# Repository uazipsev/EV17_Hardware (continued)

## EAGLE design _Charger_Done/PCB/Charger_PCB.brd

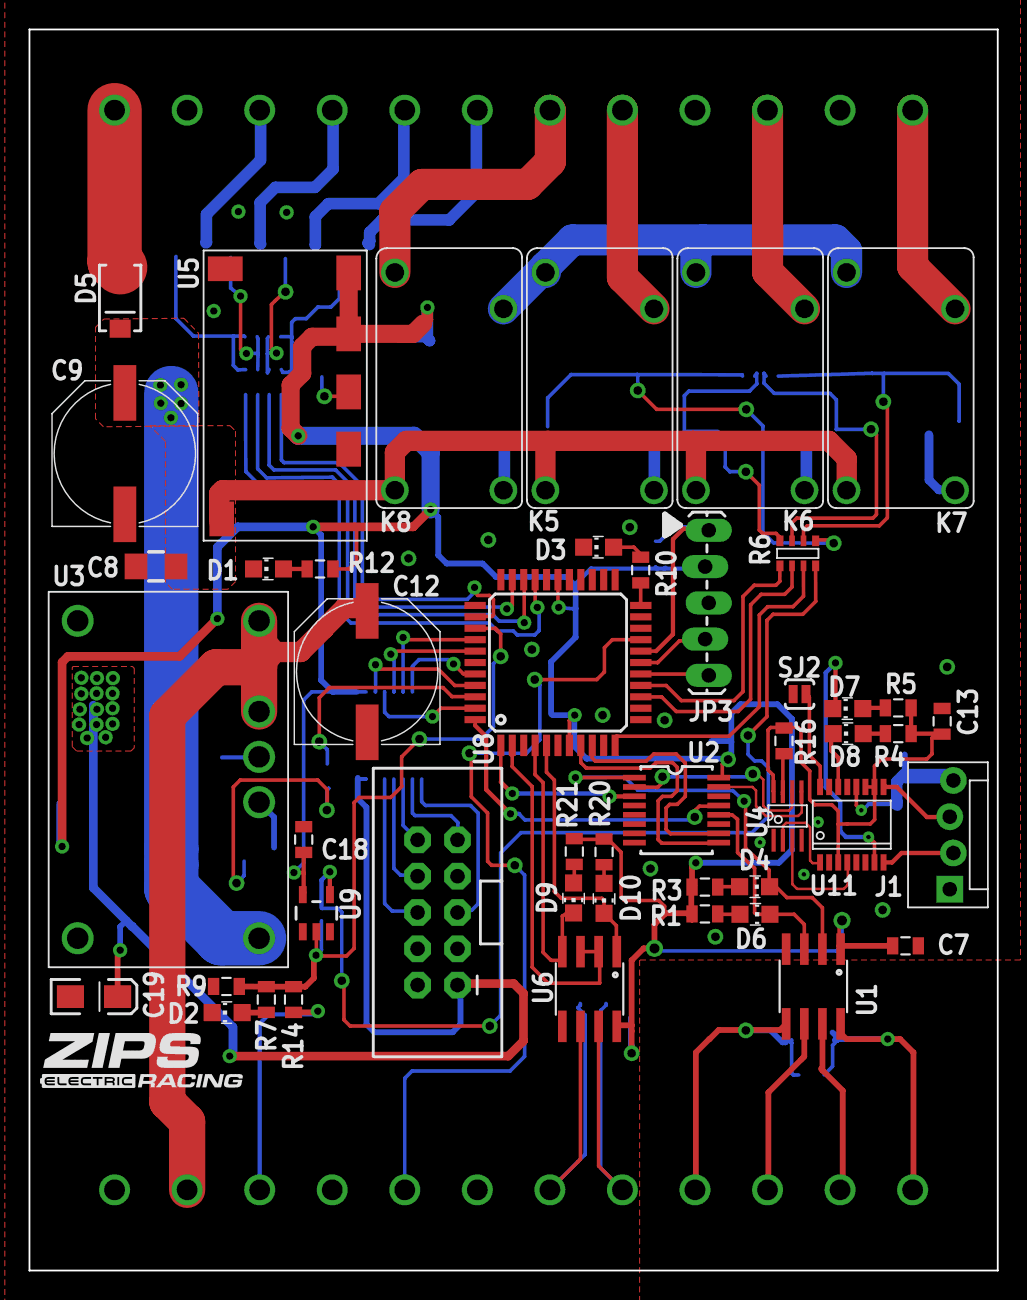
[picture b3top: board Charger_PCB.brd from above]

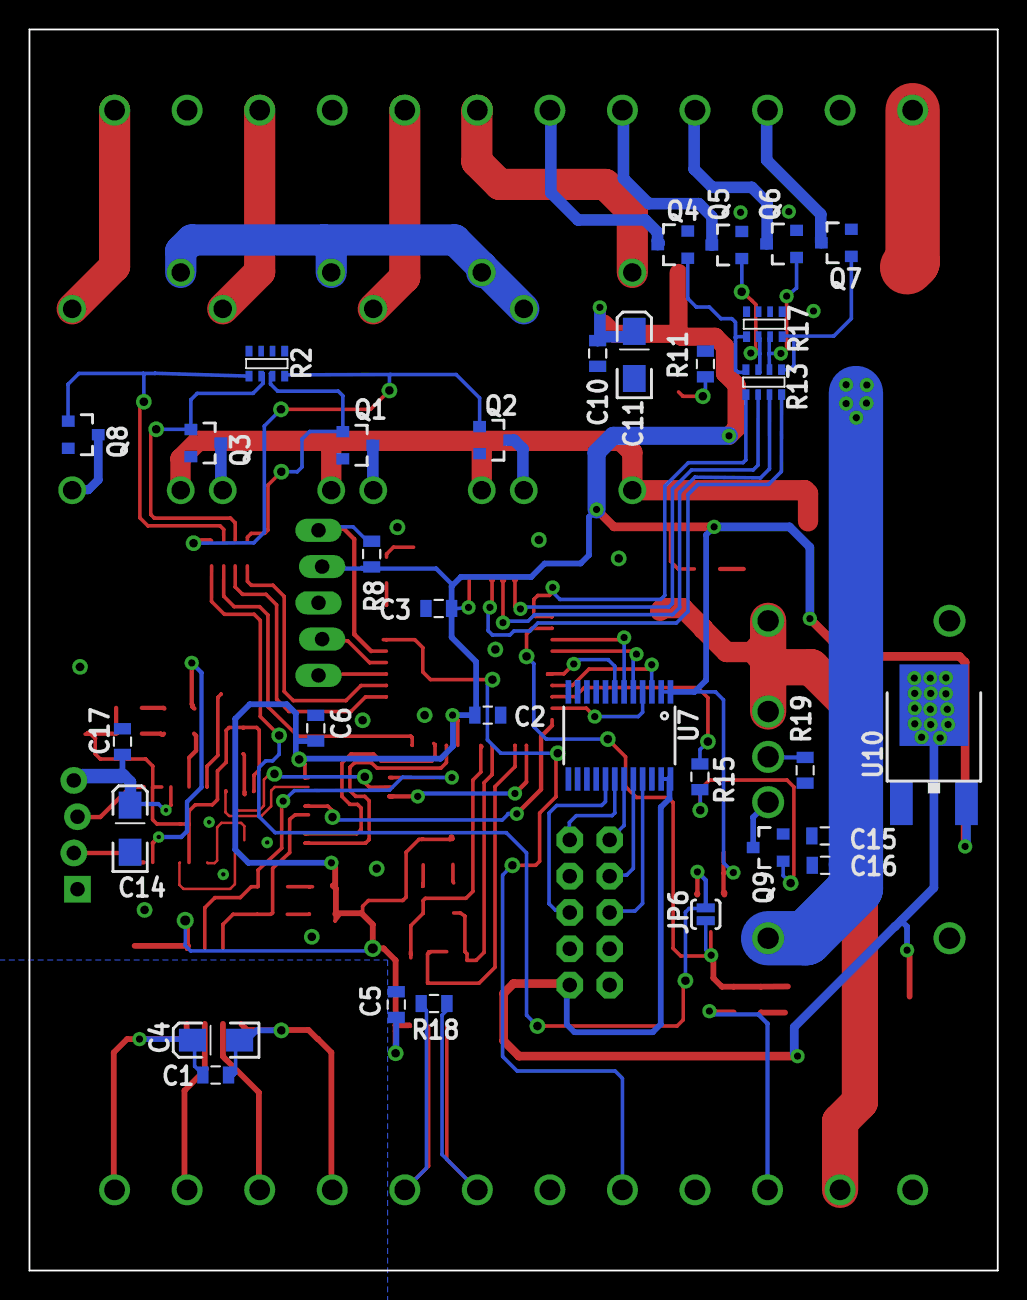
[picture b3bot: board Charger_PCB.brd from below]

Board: 2 copper layers, 67.8 x 86.9 mm, 81 parts (32 on the bottom side), 93 nets.

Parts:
C1, C2, C3, C5, C6, C7, C10, C13, C17, C18: 0.1UF; 0805
C4, C11, C14, C19: 10UF; EIA3216-16V
C8: 1UF; 1206
C9, C12: 100UF; PANASONIC-G
C15, C16: 1UF; 0805
CASE1: DMB-4772-A
D1, D2, D6, D7, D8, D9: GREEN; CHIP_LED0805
D3: AMBER; CHIP_LED0805
D4, D10: RED; CHIP_LED0805
D5: RF201L2STE25; SMA
J1: M4_1X4_LOCK; MOLEX_1X4
J2: M2X5_IDC; 3020-10-0100-00
JP3: 1X05_LOCK_LONGPADS
JP6: SJ_2S-NO
K5, K6, K7, K8: OJ-SS-124LMH2
Q1, Q2, Q3, Q8: NUD3160LT1G; SOT23
Q4, Q5, Q6, Q7, Q9: BSS123; SOT23
R1, R3, R4, R5, R7, R10, R12, R16, R20, R21: 1K; 0805
R2, R17: 10K; MNR14
R6, R13: 1K; MNR14
R8, R9, R14: 10K; 0805
R11: 16.2K; 0805
R15: 1k; 0805
R18: 120; 0805
R19: 383K; 0805
SJ2: PAD-JUMPER-2-NO_YES_SILK
U1: ISO7221; SO-8
U2: CD74HC4052PWR; TSSOP-16
U3: PTN78060HAH
U4: SN74LVC2G241; VFSOP-8
U5: APXW003A0X3-SRZ
U6: SN75HVD08DRSOIC; SO-8
U7: 74LVC8T245; TSSOP-24
U8: PIC18F45K22; TQFP-44
U9: NC7S14M5X; SOT23-5
U10: NCP1117DT_3.3; DPAK
U11: FT230X; SSOP-16
U$1: LOGO16-2-L; 2016-2-LOGO-L

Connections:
3V: C13.1, R4.2, R5.2, R16.2, U4.8, U11.3, U11.10, U11.11
!INH: R15.1, U8.42
+3V3: C19.A, J2.1, U7.23, U7.24, U10.2
+5V: C2.1, C3.1, C5.1, C6.1, C7.1, C10.1, C11.A, C18.1, JP3.2, R1.2, R3.2, R8.2, R12.2, R20.2, R21.2, U1.1, U2.16, U5.5, U5.6, U6.8, U7.1, U7.2, U8.7, U8.28, U9.5, U10.3
+12V: C12.+, CASE1.23, U3.5, U3.6
+24V: C8.1, C9.+, C15.1, C16.1, D5.C, K5.1, K6.1, K7.1, K8.1, U3.2, U5.2
AIR-TOP: R6.2, U8.14
BLUE: R13.6, U8.32
BLUE-HC: CASE1.5, Q5.3
BOTTOM: CASE1.12, K7.C
CS_3V3: J2.10, U7.19
CS_5V: U7.5, U8.38
GND: C2.2, C3.2, C5.2, C6.2, C7.2, C8.2, C9.-, C10.2, C11.C, C12.-, C13.2, C14.C, C15.2, C16.2, C17.2, C18.2, C19.C, CASE1.2, CASE1.9, CASE1.11, CASE1.19, CASE1.21, CASE1.24, D1.C, D2.C, D3.C, J1.1, J2.2, JP3.3, Q1.2, Q2.2, Q3.2, Q4.2, Q5.2, Q6.2, Q7.2, Q8.2, Q9.2, R2.1, R2.2, R2.3, R2.4, R9.1, R11.1, R17.1, R17.2, R17.3, R17.4, R19.1, SJ2.1, U1.4, U2.6, U2.7, U2.8, U3.1, U3.7, U4.1, U4.4, U5.1, U5.3, U6.5, U7.11, U7.12, U7.13, U7.22, U8.6, U8.29, U9.3, U10.1, U11.5, U11.13
GPIO: CASE1.20, U8.19, U8.20
GREEN: R13.7, U8.31
GREEN-HC: CASE1.4, Q6.3
HORN: R13.8, U8.30
HORN-HC: CASE1.3, Q7.3
IMD-R-SET: K8.2, Q2.3
IMD-R-SET1: K6.2, Q3.3
IMD-R-SET2: K5.2, Q1.3
IMD-R-SET3: K7.2, Q8.3
IMD_IN: CASE1.22, R14.2
IMD_STAT: JP6.2, R7.2, R9.2, R14.1, U8.36, U9.2
INPUT: CASE1.7, K8.NO
LCD_DC_3V3: J2.6, U7.21
LCD_DC_5V: U7.3, U8.41
LCD_RES_3V3: J2.5, U7.17
LCD_RES_5V: U7.7, U8.40
MAIN: CASE1.10, K6.C
MOSI_3V3: J2.8, U7.20
MOSI_5V: U7.4, U8.43
unnamed: D3.A, R10.1
unnamed: R10.2, U8.22
unnamed: C1.1, C4.A, CASE1.13, U1.8
unnamed: CASE1.14, U1.7
unnamed: CASE1.15, U1.6
unnamed: C1.2, C4.C, CASE1.16, U1.5
unnamed: D6.A, R1.1
unnamed: D4.A, R3.1
unnamed: D7.A, R5.1
unnamed: D8.A, R4.1
unnamed: D2.A, R7.1
unnamed: Q9.3, U3.3
unnamed: K5.NO, K6.NO, K7.NO, K8.C
unnamed: Q2.1, R2.8, R6.5
unnamed: Q8.1, R2.5, R6.6
unnamed: R11.2, U5.4
unnamed: D1.A, R12.1
unnamed: R19.2, U3.4
unnamed: Q9.1, R15.2
unnamed: D9.A, R21.1
unnamed: Q4.1, R13.4, R17.5
unnamed: D10.A, R20.1
unnamed: Q3.1, R2.6, R6.7
unnamed: Q1.1, R2.7, R6.8
unnamed: Q5.1, R13.3, R17.6
unnamed: Q6.1, R13.2, R17.7
unnamed: Q7.1, R13.1, R17.8
unnamed: SJ2.2, U11.16
unnamed: CASE1.1, D5.A
unnamed: U4.2, U11.1
unnamed: JP6.1, R6.4, U9.4
unnamed: D7.C, U11.7
unnamed: D8.C, U11.14
unnamed: U4.3, U11.4
unnamed: JP3.4, U8.17
unnamed: J1.3, U11.9
unnamed: JP3.5, U8.16
unnamed: JP3.1, R8.1, U8.18
unnamed: J1.2, U11.8
unnamed: R16.1, U4.7
unnamed: C14.A, C17.1, J1.4, U11.12
POWER: R6.1, U8.15
PRE&HV-: R6.3, U8.11
PRE-CHARGE: CASE1.8, K5.C
RS-A: CASE1.18, R18.1, U6.6
RS-B: CASE1.17, R18.2, U6.7
RX1: U2.3, U8.1
RX2: D10.C, U6.1, U8.5
RX_POWER: D4.C, U1.2, U2.1
S0: U2.10, U8.9
S1: U2.9, U8.8
SCK_3V3: J2.9, U7.18
SCK_5V: U7.6, U8.37
TX1: U2.13, U8.44
TX2: D9.C, U6.4, U8.4
TX_POWER: D6.C, U1.3, U2.12
U6-RE/DE: U6.2, U6.3, U8.2
USBRX: U2.2, U4.6
USBTX: U2.15, U4.5
YELLOW: R13.5, U8.35
YELLOW-HC: CASE1.6, Q4.3

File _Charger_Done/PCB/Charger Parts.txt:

Partlist

Exported from Charger_PCB.sch at 4/21/2016 6:51 PM

EAGLE Version 7.5.0 Copyright (c) 1988-2015 CadSoft

Assembly variant: 

Part     Value           Device                  Package                  Library             Sheet

C1       0.1UF           CAP_0.1UF_50V_0805      0805                     FSAE Electric       1
C2       0.1UF           CAP_0.1UF_50V_0805      0805                     FSAE Electric       1
C3       0.1UF           CAP_0.1UF_50V_0805      0805                     FSAE Electric       1
C4       10UF            CAP-POL_10UF_16V        EIA3216-16V              FSAE Electric       1
C5       0.1UF           CAP_0.1UF_50V_0805      0805                     FSAE Electric       1
C6       0.1UF           CAP_0.1UF_50V_0805      0805                     FSAE Electric       1
C7       0.1UF           CAP_0.1UF_50V_0805      0805                     FSAE Electric       1
C8       1UF             CAP_1UF_50V             1206                     FSAE Electric       1
C9       100UF           CAP-POL_100UF_50V_SMD   PANASONIC-G              FSAE Electric       1
C10      0.1UF           CAP_0.1UF_50V_0805      0805                     FSAE Electric       1
C11      10UF            CAP-POL_10UF_16V        EIA3216-16V              FSAE Electric       1
C12      100UF           CAP-POL_100UF_50V_SMD   PANASONIC-G              FSAE Electric       1
C13      0.1UF           CAP_0.1UF_50V_0805      0805                     FSAE Electric       1
C14      10UF            CAP-POL_10UF_16V        EIA3216-16V              FSAE Electric       1
C15      1UF             CAP_1UF_50V_0805        0805                     FSAE Electric       1
C16      1UF             CAP_1UF_50V_0805        0805                     FSAE Electric       1
C17      0.1UF           CAP_0.1UF_50V_0805      0805                     FSAE Electric       1
C18      0.1UF           CAP_0.1UF_50V_0805      0805                     FSAE Electric       2
C19      10UF            CAP-POL_10UF_16V        EIA3216-16V              FSAE Electric       1
CASE1                    DMB-4772_A              DMB-4772-A               FSAE Electric       1
D1       GREEN           LED_GREEN               CHIP_LED0805             FSAE Electric       1
D2       GREEN           LED_GREEN               CHIP_LED0805             FSAE Electric       2
D3       AMBER           LED_AMBER               CHIP_LED0805             FSAE Electric       1
D4       RED             LED_RED                 CHIP_LED0805             FSAE Electric       1
D5       RF201L2STE25    DIODE_RF201L2STE25      SMA                      FSAE Electric       1
D6       GREEN           LED_GREEN               CHIP_LED0805             FSAE Electric       1
D7       GREEN           LED_GREEN               CHIP_LED0805             FSAE Electric       1
D8       GREEN           LED_GREEN               CHIP_LED0805             FSAE Electric       1
D9       GREEN           LED_GREEN               CHIP_LED0805             FSAE Electric       1
D10      RED             LED_RED                 CHIP_LED0805             FSAE Electric       1
J1       M4_1X4_LOCK     M4_1X4_LOCK             MOLEX_1X4                FSAE Electric       1
J2       M2X5_IDC        M2X5_IDC                3020-10-0100-00          FSAE Electric       1
JP3                      M05LOCK_LONGPADS        1X05_LOCK_LONGPADS       SparkFun-Connectors 1
JP6                      JUMPER-2SMD-NO          SJ_2S-NO                 SparkFun-Passives   2
K5       OJ-SS-124LMH2   OJ-SS-124LMH2           OJ-SS-124LMH2            FSAE Electric       2
K6       OJ-SS-124LMH2   OJ-SS-124LMH2           OJ-SS-124LMH2            FSAE Electric       2
K7       OJ-SS-124LMH2   OJ-SS-124LMH2           OJ-SS-124LMH2            FSAE Electric       2
K8       OJ-SS-124LMH2   OJ-SS-124LMH2           OJ-SS-124LMH2            FSAE Electric       2
Q1       NUD3160LT1G     NUD3160LT1G             SOT23                    FSAE Electric       2
Q2       NUD3160LT1G     NUD3160LT1G             SOT23                    FSAE Electric       2
Q3       NUD3160LT1G     NUD3160LT1G             SOT23                    FSAE Electric       2
Q4       BSS123          MOS-N_BSS123            SOT23                    FSAE Electric       2
Q5       BSS123          MOS-N_BSS123            SOT23                    FSAE Electric       2
Q6       BSS123          MOS-N_BSS123            SOT23                    FSAE Electric       2
Q7       BSS123          MOS-N_BSS123            SOT23                    FSAE Electric       2
Q8       NUD3160LT1G     NUD3160LT1G             SOT23                    FSAE Electric       2
Q9       BSS123          MOS-N_BSS123            SOT23                    FSAE Electric       1
R1       1K              RES_1K_1%_0805          0805                     FSAE Electric       1
R2       10K             RN-4_10K                MNR14                    FSAE Electric       2
R3       1K              RES_1K_1%_0805          0805                     FSAE Electric       1
R4       1K              RES_1K_1%_0805          0805                     FSAE Electric       1
R5       1K              RES_1K_1%_0805          0805                     FSAE Electric       1
R6       1K              RN-4_1K                 MNR14                    FSAE Electric       2
R7       1K              RES_1K_1%_0805          0805                     FSAE Electric       2
R8       10K             RES_10K_1%_0805         0805                     FSAE Electric       1
R9       10K             RES_10K_1%_0805         0805                     FSAE Electric       2
R10      1K              RES_1K_1%_0805          0805                     FSAE Electric       1
R11      16.2K           RES_16.2K_1%_0805       0805                     FSAE Electric       1
R12      1K              RES_1K_1%_0805          0805                     FSAE Electric       1
R13      1K              RN-4_1K                 MNR14                    FSAE Electric       2
R14      10K             RES_10K_1%_0805         0805                     FSAE Electric       2
R15      1k              RES_1K_1%_0805          0805                     FSAE Electric       1
R16      1K              RES_1K_1%_0805          0805                     FSAE Electric       1
R17      10K             RN-4_10K                MNR14                    FSAE Electric       2
R18      120             RES_120_1%_0805         0805                     FSAE Electric       1
R19      383K            RES_383K_1%_0805        0805                     FSAE Electric       1
R20      1K              RES_1K_1%_0805          0805                     FSAE Electric       1
R21      1K              RES_1K_1%_0805          0805                     FSAE Electric       1
SJ2                      JUMPER-PAD-2-NOYES_SILK PAD-JUMPER-2-NO_YES_SILK SparkFun-Passives   1
U1       ISO7221         ISO7221                 SO-8                     FSAE Electric       1
U2       CD74HC4052PWR   CD74HC4052PWR           TSSOP-16                 FSAE Electric       1
U3       PTN78060HAH     PTN78060HAH             PTN78060HAH              FSAE Electric       1
U4       SN74LVC2G241    SN74LVC2G241            VFSOP-8                  FSAE Electric       1
U5       APXW003A0X3-SRZ APXW003A0X3-SRZ         APXW003A0X3-SRZ          FSAE Electric       1
U6       SN75HVD08DRSOIC SN75HVD08DRSOIC         SO-8                     FSAE Electric       1
U7       74LVC8T245      74LVC8T245              TSSOP-24                 FSAE Electric       1
U8       PIC18F45K22     PIC18F45K22             TQFP-44                  FSAE Electric       1
U9       NC7S14M5X       NC7S14M5X               SOT23-5                  FSAE Electric       2
U10      NCP1117DT_3.3   NCP1117DT_3.3           DPAK                     FSAE Electric       1
U11      FT230X          FT230X                  SSOP-16                  FSAE Electric       1

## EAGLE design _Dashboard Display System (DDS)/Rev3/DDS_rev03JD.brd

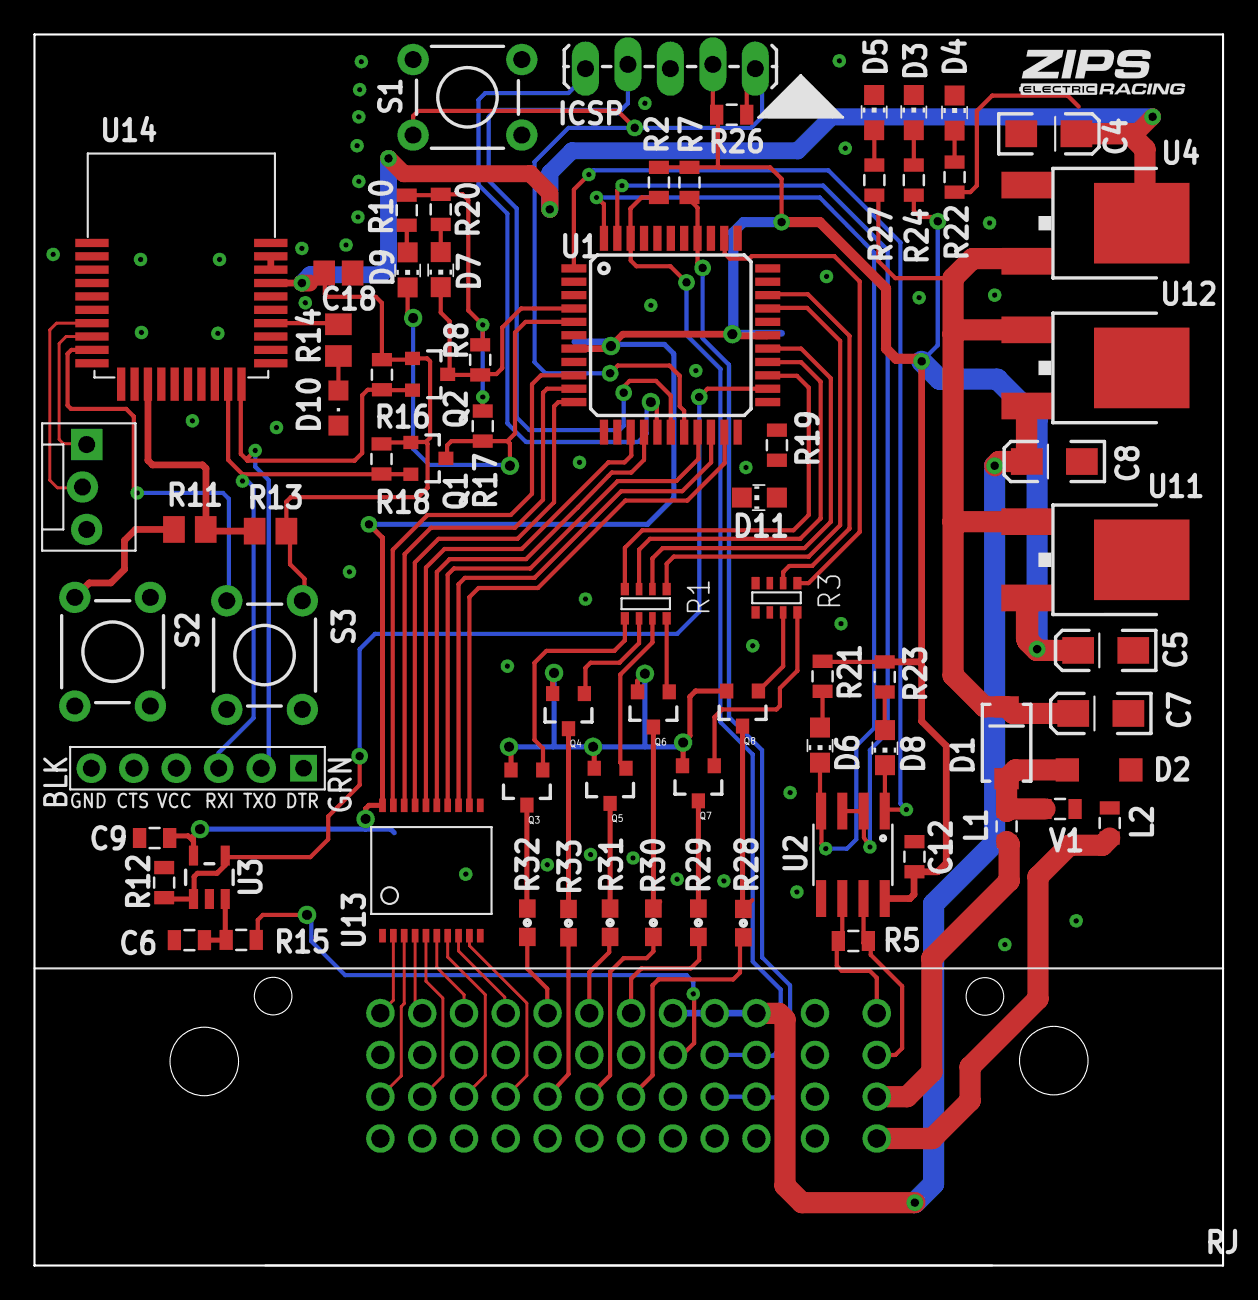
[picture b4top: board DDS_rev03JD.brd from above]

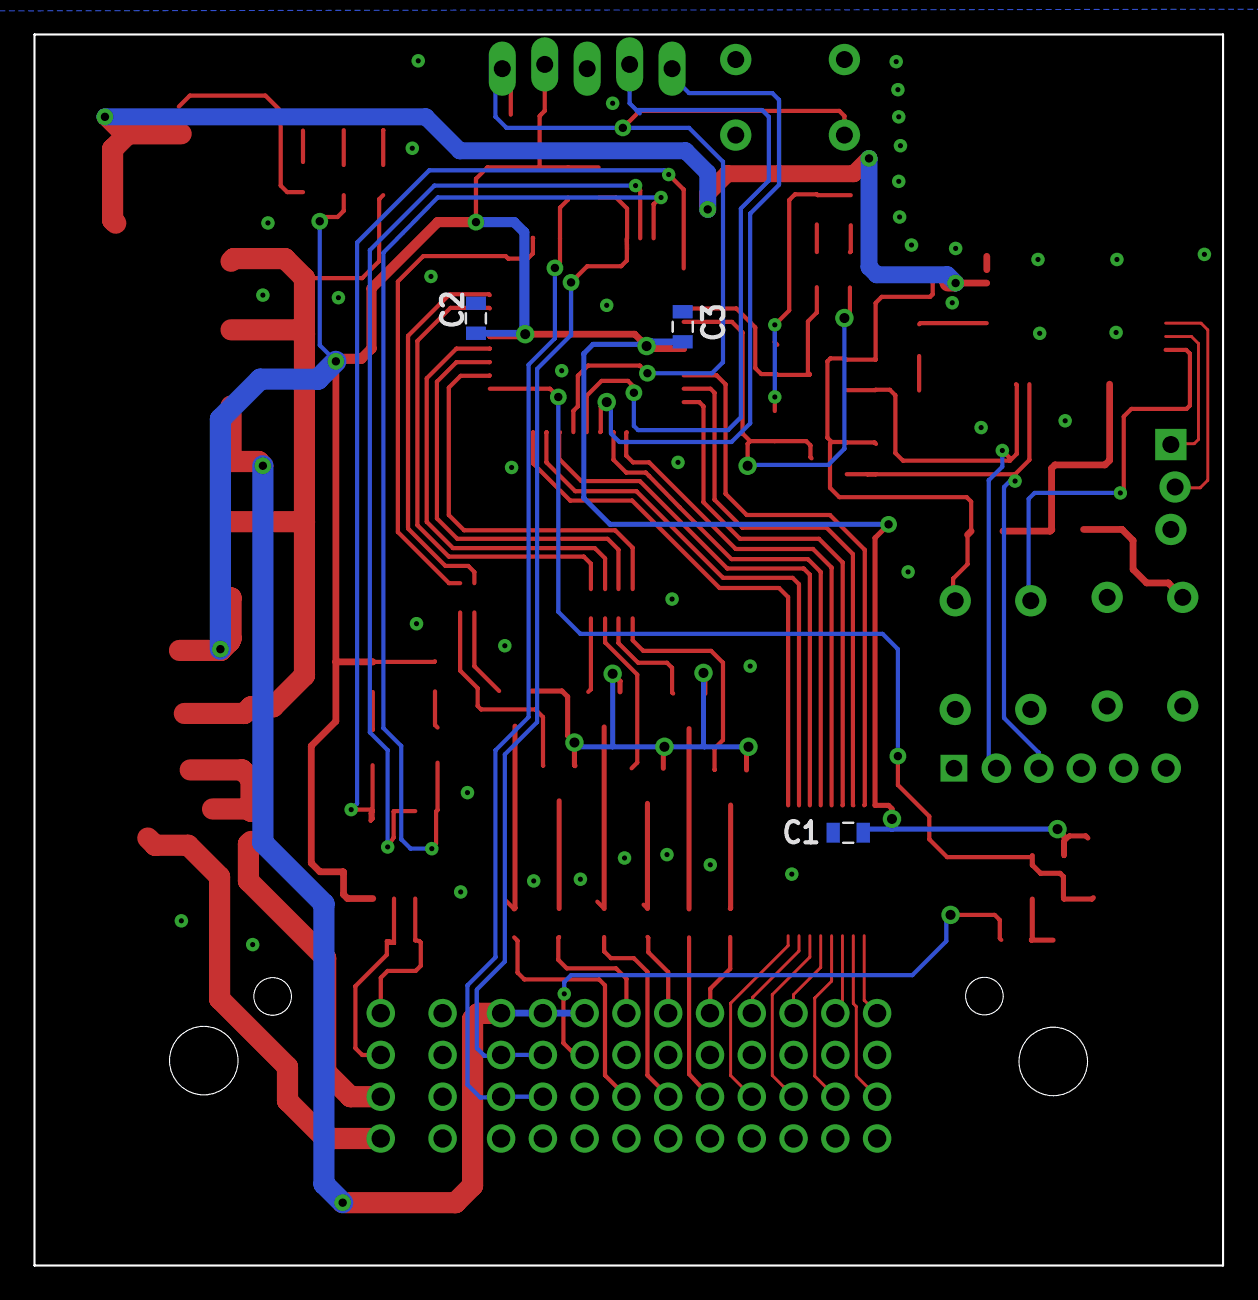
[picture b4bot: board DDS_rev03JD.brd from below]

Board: 2 copper layers, 71.1 x 73.7 mm, 79 parts (3 on the bottom side), 82 nets.

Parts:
C1, C2, C3, C9, C12: \0.1UF; 0805
C4, C5, C7, C8: 10UF; EIA3216-16V
C6: 1UF; 0805
C18: 0.1uF; C0805
D1: S1B; SMA
D2: 11V; SOD-123
D3, D4, D5, D6, D7: GREEN; CHIP_LED0805
D8, D9: RED; CHIP_LED0805
D10: CHIPLED_0805
D11: AMBER; CHIP_LED0805
ICSP: 1X05_LOCK_LONGPADS
J1: 36638NEW; 36638-M
JP1: MOLEX-1X3_LOCK
JP19: FTDI_DEVICE; FTDI_DEVICE_SIDE
L1, L2: L_FB_2A; 0805
Q1, Q2: BSS123; SOT23
Q3, Q4, Q5, Q6, Q7, Q8: PNP_MMBT4403LT3G; SOT23
R1, R3: RN-4_2.2K; MNR14
R2, R7: 2.2K; 0805
R5: 120; 0805
R8, R12, R15, R16, R17, R18, R26: 10K; 0805
R10, R19, R20, R21, R23, R24: 1K; 0805
R11, R14: 1K; M0805
R13: 10K; M0805
R22: 330; 0805
R27: 1.2K; 0805
R28, R29, R30, R31, R32, R33: RESPLACEHOLDER; 0603
S1: SWITCH-MOMENTARY-2PTH; TACTILE-PTH
S2: NO; TACTILE-PTH
S3: TACTILE-PTH
U1: PIC18F45K22; TQFP-44
U2: SN75HVD08DRSOIC; SO-8
U3: OPA344; SOT23-5
U4: NCP1117DT_3.3; DPAK
U11, U12: NCV7805BDTRKG; DPAK
U13: MAX6818; SSOP-20
U14: A20737AGM
U$1: INDPK1; PICKIT-PIN-1
U$3: LOGO16-2-M; 2016-2-LOGO-M
V1: 10.8V; 0805

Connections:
5V2: C8.A, J1.29, J1.33, J1.37, U12.3
+: J1.47, L1.1
+3V3: C4.A, C18.1, Q1.1, Q2.1, R13.2, R16.2, R18.2, R22.2, S3.1, U4.2, U14.27
+5V: C1.1, C2.1, C3.1, C5.A, C9.1, C12.1, ICSP.2, R2.2, R7.2, R8.2, R10.2, R17.2, R20.2, R21.2, R23.2, R24.2, R26.2, U1.7, U1.28, U2.8, U3.5, U11.3, U13.20
+9V: C7.A, D1.C, Q3.2, Q4.2, Q5.2, Q6.2, Q7.2, Q8.2, R27.2, U4.3, U11.1, U12.1
-: J1.48, L2.1
ACK: J1.15, U13.9
BLE-RX: JP19.P$2, Q2.2, R16.1, U14.20
BLE-TX: JP19.P$3, Q1.2, R18.1, U14.19
BLE_RESET: R11.2, R13.1, U14.13
GHT: D1.A, D2.C, L1.2, V1.1
GND: C1.2, C2.2, C3.2, C4.C, C5.C, C6.2, C7.C, C8.C, C9.2, C12.2, C18.2, D2.A, D3.C, D4.C, D5.C, D10.C, D11.C, ICSP.3, J1.2, J1.4, J1.6, J1.8, J1.10, J1.12, J1.14, J1.16, J1.18, J1.20, J1.22, J1.24, J1.26, J1.28, J1.32, J1.36, J1.40, JP1.3, JP19.P$6, L2.2, R12.1, S1.1, S2.1, U1.6, U1.29, U2.5, U3.2, U4.1, U11.2, U12.2, U13.1, U13.10, U14.1, U14.3, U14.6, U14.11, U14.30, V1.2
LED0: R3.1, U1.35
LED1: R3.2, U1.31
LED2: R1.1, U1.30
LED3: R1.2, U1.27
LED4: R1.3, U1.26
LED5: R1.4, U1.25
unnamed: D11.A, R19.1
unnamed: R19.2, U1.22
unnamed: J1.30, R15.2
unnamed: J1.1, U13.2
unnamed: Q8.3, R28.1
unnamed: R14.2, U14.24
unnamed: Q3.1, R1.5
unnamed: Q6.1, R1.8
unnamed: Q4.1, R1.6
unnamed: Q5.1, R1.7
unnamed: D6.A, R21.1
unnamed: Q7.1, R3.8
unnamed: Q8.1, R3.7
unnamed: D8.A, R23.1
unnamed: D5.A, R27.1
unnamed: D9.A, R10.1
unnamed: D7.A, R20.1
unnamed: D3.A, R24.1
unnamed: Q7.3, R29.1
unnamed: D4.A, R22.1
unnamed: C6.1, R15.1, U3.3
unnamed: Q6.3, R30.1
unnamed: Q5.3, R31.1
unnamed: Q3.3, R32.1
unnamed: Q4.3, R33.1
unnamed: ICSP.4, U1.17
unnamed: ICSP.5, U1.16
unnamed: ICSP.1, R26.1, S1.3, U1.18
unnamed: J1.3, U13.3
unnamed: J1.5, U13.4
unnamed: J1.7, U13.5
unnamed: J1.9, U13.6
unnamed: J1.11, U13.7
unnamed: U14.28, U14.29
unnamed: R11.1, S2.3
unnamed: D10.A, R14.1
unnamed: JP1.1, U14.8
unnamed: JP1.2, U14.7
unnamed: S3.3, U14.9
RS-A: J1.45, R5.1, U2.6
RS-B: J1.46, R5.2, U2.7
RX1: D8.C, U1.1, U2.1
RX2: D9.C, Q1.3, R17.1, U1.5
SCL: J1.35, J1.39, R7.1, U1.37
SDA: J1.34, J1.38, R2.1, U1.42
S_IN_1: U1.21, U13.12
S_IN_2: U1.20, U13.13
S_IN_3: U1.19, U13.14
S_IN_4: U1.15, U13.15
S_IN_5: U1.14, U13.16
S_IN_6: U1.11, U13.17
S_IN_7: U1.10, U13.18
S_IN_8: U1.9, U13.19
TALK: J1.13, U13.8
TX1: D6.C, U1.44, U2.4
TX2: D7.C, Q2.3, R8.1, U1.4
U2-RE/DE: U1.43, U2.2, U2.3
VOL: R12.2, U1.24, U3.1, U3.4
_OLED0: J1.17, R32.2
_OLED1: J1.19, R33.2
_OLED2: J1.21, R31.2
_OLED3: J1.23, R30.2
_OLED4: J1.25, R29.2
_OLED5: J1.27, R28.2

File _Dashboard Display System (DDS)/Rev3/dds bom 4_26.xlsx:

DDS BOM 4-27
Part | Value | Package
R5 | 120 | 805
R11, R13, R22 | 330 | 805
C1, C2, C3, C9, C11, C12 | \0.1UF | 805
R27 | 1.2K | 805
V1 | 10.8V | 805
R14 | 100K | 805
R4, R8, R12, R15, R16, R17, R18, R26 | 10K | MNR14
C4, C5, C7, C8, C10 | 10UF | EIA3216-16V
D2 | 11V | SOD-123
R1, R6, R9, R10, R19, R20, R21, R23, R24 | 1K | MNR14
C6 | 1UF | 805
R2, R7 | 2.2K | 805
J1 | 36638NEW | 36638-M
D10, D11 | AMBER | CHIP_LED0805
U$2 | BLUETOOTH- | RN41" RN41
Q1, Q2 | BSS123 | SOT23
U5, U6, U7, U8, U9, U10 | DMG6602SVT | Q SOT23-6
D3, D4, D5, D6, D7 | GREEN | CHIP_LED0805
L1, L2 | L_FB_2A | 805
U13 | MAX6818 | SSOP-20
U4 | NCP1117DT_ | 3.3 DPAK
U11, U12 | NCV7805BDT | RKG DPAK
U3 | OPA344 | SOT23-5
U1 | PIC18F45K2 | 2 TQFP-44
D8, D9 | RED | CHIP_LED0805
R28, R29, R30, R31, R32, R33 | RESPLACEHO | LDER 0603
R3, R25 | RN-4_10K | MNR14
D1 | S1B | SMA
U2 | SN75HVD08D | RSOIC SO-8
D12 | YELLOW | CHIP_LED0805
JP3 |  | 1X05_LOCK_LONGPADS

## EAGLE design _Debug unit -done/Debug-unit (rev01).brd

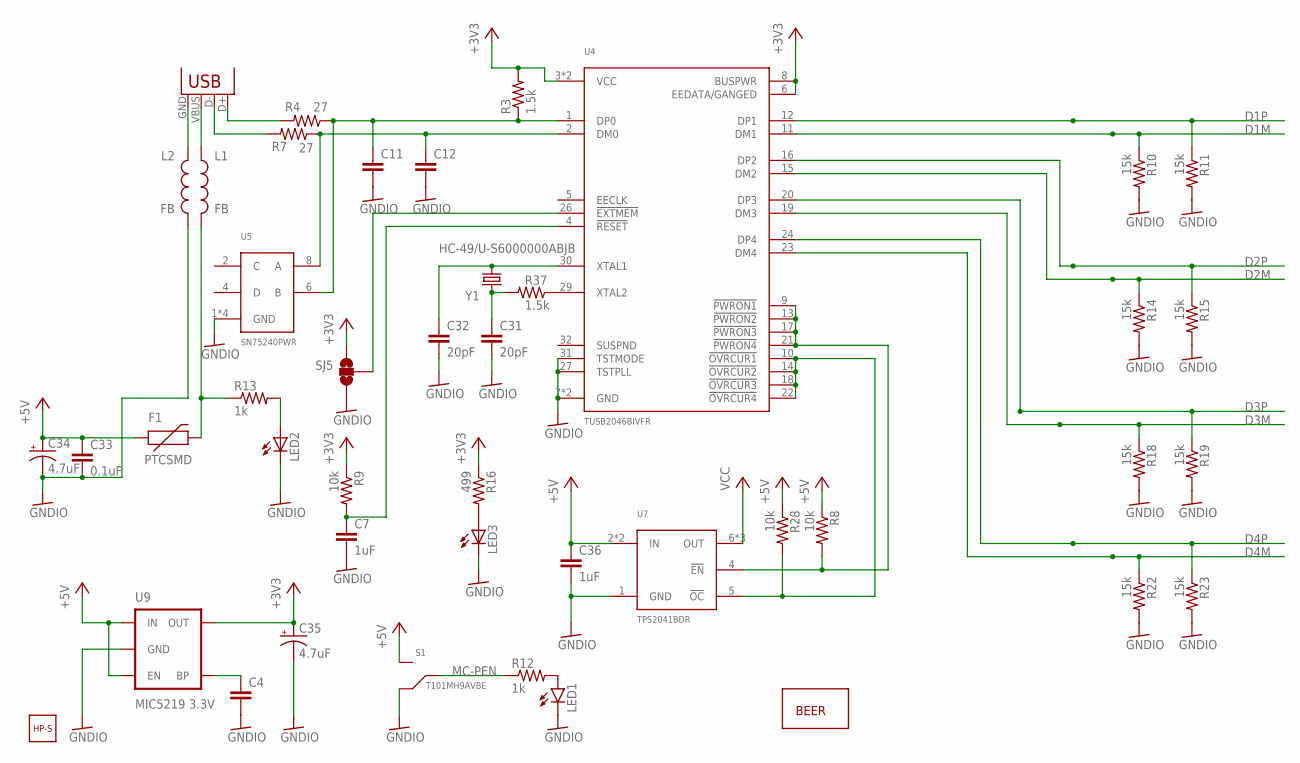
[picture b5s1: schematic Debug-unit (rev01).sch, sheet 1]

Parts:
C4, C11, C12: CAP0805; 0805
C7, C36: 1uF; 0805
C31, C32: 20pF; 0805
C33: 0.1uF; 0805
C34, C35: 4.7uF; EIA3216
F1: PTCSMD; PTC-1206
JP9: USB-B; USB-B-PTH
L1, L2: FB; 0805
LED1: LED-3MM-NO_SILK; LED3MM-NS
LED2, LED3: LEDCHIP-LED0805; CHIP-LED0805
R3, R37: 1.5k; 0805
R4, R7: 27; 0805
R8, R9, R28: 10k; 0805
R10, R11, R14, R15, R18, R19, R22, R23: 15k; 0805
R12, R13: 1k; 0805
R16: 499; 0805
S1: T101MH9AVBE
SJ5: JUMPER-PAD-3-NOFULL_BOX_SILK; PAD-JUMPER-3-NO_YES_SILK_FULL_BOX
U4: TUSB2046BIVFR; LQFP-32
U5: SN75240PWR; TSSOP-8
U7: TPS2041BDR; SO-8
U9: MIC5219 3.3V; SOT23-5
U$1: HP-3651-B
U$3: BEERS; B-S
Y1: HC-49/U-S6000000ABJB; HC49US

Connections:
+3V3: C35.A (+), R3.2, R9.1, R16.1, SJ5.1, U4.3 (VCC), U4.6 (EEDATA/GANGED), U4.8 (BUSPWR), U4.25 (VCC), U9.5 (OUT)
+5V: C33.1, C34.A (+), C36.1, F1.1, R8.1, R28.1, S1.1 (NO), U7.2 (IN), U7.3 (IN), U9.1 (IN), U9.3 (EN)
D1M: R10.1, U4.11 (DM1); also elsewhere on the board
D1P: R11.1, U4.12 (DP1); also elsewhere on the board
D2M: R14.1, U4.15 (DM2); also elsewhere on the board
D2P: R15.1, U4.16 (DP2); also elsewhere on the board
D3M: R18.1, U4.19 (DM3); also elsewhere on the board
D3P: R19.1, U4.20 (DP3); also elsewhere on the board
D4M: R22.1, U4.23 (DM4); also elsewhere on the board
D4P: R23.1, U4.24 (DP4); also elsewhere on the board
GNDIO: C4.2, C7.2, C11.2, C12.2, C31.2, C32.2, C33.2, C34.C (-), C35.C (-), C36.2, L2.2, LED1.K (C), LED2.C, LED3.C, R10.2, R11.2, R14.2, R15.2, R18.2, R19.2, R22.2, R23.2, S1.3 (NC), SJ5.3, U4.7 (GND), U4.27 (TSTPLL), U4.28 (GND), U4.31 (TSTMODE), U5.1 (GND), U5.3 (GND), U5.5 (GND), U5.7 (GND), U7.1 (GND), U9.2 (GND); also elsewhere on the board
MC-PEN: R12.1, S1.2 (C); also elsewhere on the board
unnamed: C4.1, U9.4 (BP)
unnamed: R8.2, U4.9 (!PWRON1), U4.13 (!PWRON2), U4.17 (!PWRON3), U4.21 (!PWRON4), U7.4 (!EN)
unnamed: LED2.A, R13.2
unnamed: LED3.A, R16.2
unnamed: R28.2, U4.10 (!OVRCUR1), U4.14 (!OVRCUR2), U4.18 (!OVRCUR3), U4.22 (!OVRCUR4), U7.5 (!OC)
unnamed: R37.1, U4.29 (XTAL2)
unnamed: C31.1, R37.2, Y1.2
unnamed: C32.1, U4.30 (XTAL1), Y1.1
unnamed: C11.1, R3.1, R4.1, U4.1 (DP0), U5.6 (B)
unnamed: SJ5.2, U4.26 (!EXTMEM)
unnamed: C12.1, R7.1, U4.2 (DM0), U5.8 (A)
unnamed: JP9.D+, R4.2
unnamed: JP9.D-, R7.2
unnamed: C7.1, R9.2, U4.4 (!RESET)
unnamed: JP9.VBUS, L1.1
unnamed: JP9.GND, L2.1
unnamed: F1.2, L1.2, R13.1
unnamed: LED1.A, R12.2
VCC: U7.6 (OUT), U7.7 (OUT), U7.8 (OUT); also elsewhere on the board

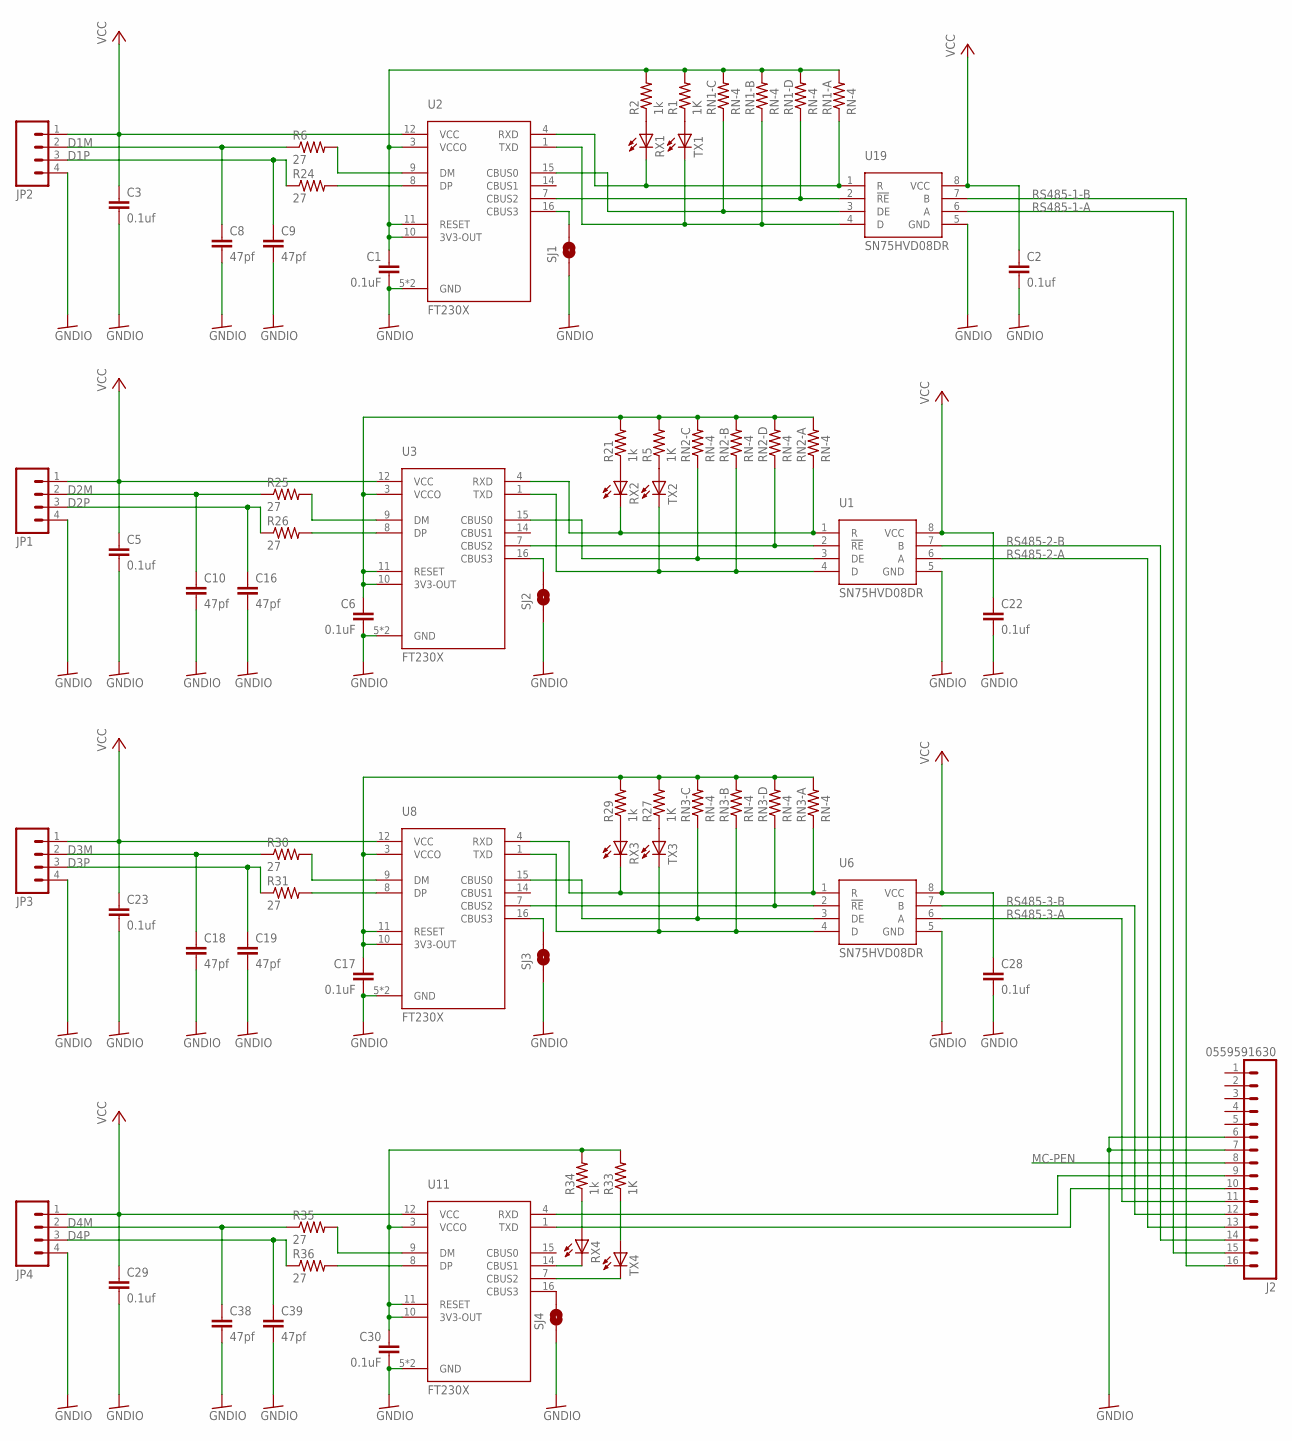
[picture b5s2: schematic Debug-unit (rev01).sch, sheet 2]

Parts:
C1, C6, C17, C30: 0.1uF; 0805
C2, C3, C5, C22, C23, C28, C29: 0.1uf; 0805
C8, C9, C10, C16, C18, C19, C38, C39: 47pf; 0805
J2: 0559591630
JP1, JP2, JP3, JP4: M04POLAR_LOCK; MOLEX-1X4_LOCK
R1, R5, R27, R33: 1K; R0805
R2, R21, R29, R34: 1k; R0805
R6, R24, R25, R26, R30, R31, R35, R36: 27; 0805
RN1, RN2, RN3: RN-4; CRA06S
RX1, RX2, RX3, RX4: LEDCHIPLED_0805; CHIPLED_0805
SJ1, SJ2, SJ3, SJ4: JUMPER-PAD-2-NOYES_SILK; PAD-JUMPER-2-NO_YES_SILK
TX1, TX2, TX3, TX4: LEDCHIPLED_0805; CHIPLED_0805
U1, U6, U19: SN75HVD08DR; SO-8
U2, U3, U8, U11: FT230X; SSOP-16

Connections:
3V: C1.1, R1.2, R2.2, RN1.5 (2), RN1.6 (2), RN1.7 (2), RN1.8 (2), U2.3 (VCCO), U2.10 (3V3-OUT), U2.11 (RESET)
3V1: C6.1, R5.2, R21.2, RN2.5 (2), RN2.6 (2), RN2.7 (2), RN2.8 (2), U3.3 (VCCO), U3.10 (3V3-OUT), U3.11 (RESET)
3V2: C17.1, R27.2, R29.2, RN3.5 (2), RN3.6 (2), RN3.7 (2), RN3.8 (2), U8.3 (VCCO), U8.10 (3V3-OUT), U8.11 (RESET)
3V3: C30.1, R33.2, R34.2, U11.3 (VCCO), U11.10 (3V3-OUT), U11.11 (RESET)
D1M: C8.1, JP2.2, R6.1; also elsewhere on the board
D1P: C9.1, JP2.3, R24.1; also elsewhere on the board
D2M: C10.1, JP1.2, R25.1; also elsewhere on the board
D2P: C16.1, JP1.3, R26.1; also elsewhere on the board
D3M: C18.1, JP3.2, R30.1; also elsewhere on the board
D3P: C19.1, JP3.3, R31.1; also elsewhere on the board
D4M: C38.1, JP4.2, R35.1; also elsewhere on the board
D4P: C39.1, JP4.3, R36.1; also elsewhere on the board
GNDIO: C1.2, C2.2, C3.2, C5.2, C6.2, C8.2, C9.2, C10.2, C16.2, C17.2, C18.2, C19.2, C22.2, C23.2, C28.2, C29.2, C30.2, C38.2, C39.2, J2.6, J2.7, JP1.4, JP2.4, JP3.4, JP4.4, SJ1.1, SJ2.1, SJ3.1, SJ4.1, U1.5 (GND), U2.5 (GND), U2.13 (GND), U3.5 (GND), U3.13 (GND), U6.5 (GND), U8.5 (GND), U8.13 (GND), U11.5 (GND), U11.13 (GND), U19.5 (GND); also elsewhere on the board
MC-PEN: J2.8; also elsewhere on the board
unnamed: R1.1, TX1.A
unnamed: R2.1, RX1.A
unnamed: SJ1.2, U2.16 (CBUS3)
unnamed: R5.1, TX2.A
unnamed: RN1.4 (1), U2.7 (CBUS2), U19.2 (!RE)
unnamed: RN1.3 (1), U2.15 (CBUS0), U19.3 (DE)
unnamed: R6.2, U2.9 (DM)
unnamed: R24.2, U2.8 (DP)
unnamed: R21.1, RX2.A
unnamed: R25.2, U3.9 (DM)
unnamed: R26.2, U3.8 (DP)
unnamed: RN2.4 (1), U1.2 (!RE), U3.7 (CBUS2)
unnamed: RN2.3 (1), U1.3 (DE), U3.15 (CBUS0)
unnamed: SJ2.2, U3.16 (CBUS3)
unnamed: R27.1, TX3.A
unnamed: R29.1, RX3.A
unnamed: R30.2, U8.9 (DM)
unnamed: R31.2, U8.8 (DP)
unnamed: RN3.4 (1), U6.2 (!RE), U8.7 (CBUS2)
unnamed: RN3.3 (1), U6.3 (DE), U8.15 (CBUS0)
unnamed: SJ3.2, U8.16 (CBUS3)
unnamed: R33.1, TX4.A
unnamed: R34.1, RX4.A
unnamed: TX4.C, U11.7 (CBUS2)
unnamed: RX4.C, U11.14 (CBUS1)
unnamed: R35.2, U11.9 (DM)
unnamed: R36.2, U11.8 (DP)
unnamed: SJ4.2, U11.16 (CBUS3)
unnamed: J2.10, U11.1 (TXD)
unnamed: J2.9, U11.4 (RXD)
RS485-1-A: J2.15, U19.6 (A)
RS485-1-B: J2.16, U19.7 (B)
RS485-2-A: J2.13, U1.6 (A)
RS485-2-B: J2.14, U1.7 (B)
RS485-3-A: J2.11, U6.6 (A)
RS485-3-B: J2.12, U6.7 (B)
RXD0: RN1.1, RX1.C, U2.4 (RXD), U19.1 (R)
RXD1: RN2.1, RX2.C, U1.1 (R), U3.4 (RXD)
RXD2: RN3.1, RX3.C, U6.1 (R), U8.4 (RXD)
TXD0: RN1.2 (1), TX1.C, U2.1 (TXD), U19.4 (D)
TXD1: RN2.2 (1), TX2.C, U1.4 (D), U3.1 (TXD)
TXD2: RN3.2 (1), TX3.C, U6.4 (D), U8.1 (TXD)
VCC: C2.1, C3.1, C5.1, C22.1, C23.1, C28.1, C29.1, JP1.1, JP2.1, JP3.1, JP4.1, U1.8 (VCC), U2.12 (VCC), U3.12 (VCC), U6.8 (VCC), U8.12 (VCC), U11.12 (VCC), U19.8 (VCC); also elsewhere on the board
